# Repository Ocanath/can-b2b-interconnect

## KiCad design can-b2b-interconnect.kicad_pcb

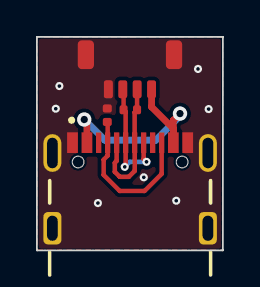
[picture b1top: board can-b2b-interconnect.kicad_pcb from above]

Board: 2 copper layers, 10.3 x 11.9 mm, 4 parts (0 on the bottom side), 5 nets.

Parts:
J2: USB4110GFA; GCT_USB4105-GF-A
R1: 120 0402; R_0402_1005Metric
R3: 5.1k; R_0402_1005Metric
U1: DF52-4S-0.8H(21)

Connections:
/CANH: J2.A6 (DP1), J2.B6 (DP2), R1.2, U1.3
/CANL: J2.A7 (DN1), J2.B7 (DN2), R1.1, U1.2
/VBAT: J2.A4/B9 (VBUS), J2.B4/A9 (VBUS__1), U1.1
GND: J2.A1/B12 (GND), J2.B1/A12 (GND__1), J2.S1 (GND__2), J2.S2 (GND__3), J2.S3 (GND__4), J2.S4 (GND__5), R3.1, U1.4, U1.5 (MNT), U1.6 (MNT)
unnamed: J2.A5 (CC1), J2.B5 (CC2), R3.2

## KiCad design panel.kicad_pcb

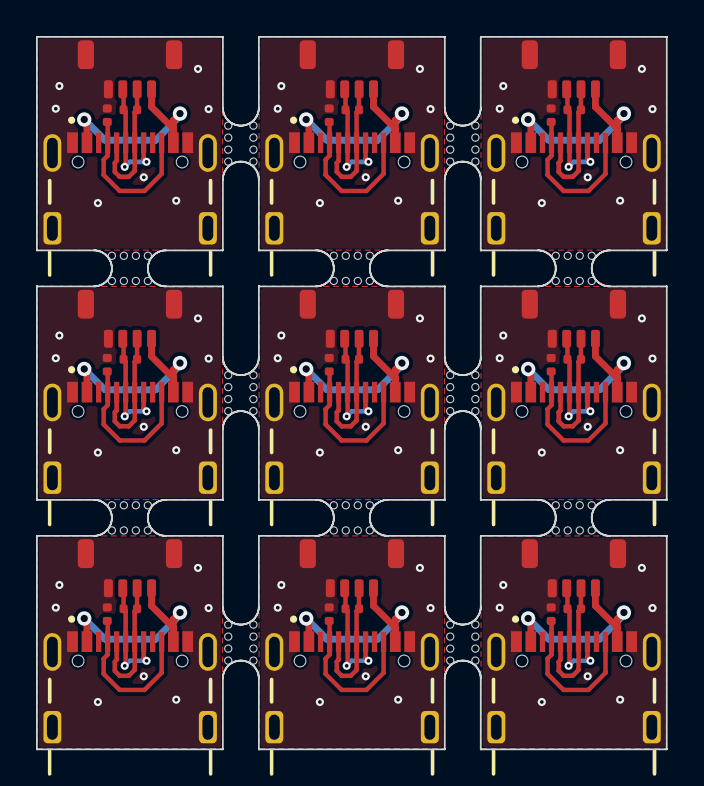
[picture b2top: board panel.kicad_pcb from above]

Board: 2 copper layers, 35.0 x 39.6 mm, 132 parts (0 on the bottom side), 45 nets.

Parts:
J2, J2#2, J2#3, J2#4, J2#5, J2#6, J2#7, J2#8, J2#9: USB4110GFA; GCT_USB4105-GF-A
KiKit_MB_1_1, KiKit_MB_1_2, KiKit_MB_1_3, KiKit_MB_1_4, KiKit_MB_2_1, KiKit_MB_2_2, KiKit_MB_2_3, KiKit_MB_2_4, KiKit_MB_3_1, KiKit_MB_3_2, KiKit_MB_3_3, KiKit_MB_3_4, KiKit_MB_4_1, KiKit_MB_4_2, KiKit_MB_4_3, KiKit_MB_4_4, KiKit_MB_5_1, KiKit_MB_5_2, KiKit_MB_5_3, KiKit_MB_5_4, KiKit_MB_6_1, KiKit_MB_6_2, KiKit_MB_6_3, KiKit_MB_6_4, KiKit_MB_7_1, KiKit_MB_7_2, KiKit_MB_7_3, KiKit_MB_7_4, KiKit_MB_8_1, KiKit_MB_8_2, KiKit_MB_8_3, KiKit_MB_8_4, KiKit_MB_9_1, KiKit_MB_9_2, KiKit_MB_9_3, KiKit_MB_9_4, KiKit_MB_10_1, KiKit_MB_10_2, KiKit_MB_10_3, KiKit_MB_10_4, KiKit_MB_11_1, KiKit_MB_11_2, KiKit_MB_11_3, KiKit_MB_11_4, KiKit_MB_12_1, KiKit_MB_12_2, KiKit_MB_12_3, KiKit_MB_12_4, KiKit_MB_13_1, KiKit_MB_13_2, KiKit_MB_13_3, KiKit_MB_13_4, KiKit_MB_14_1, KiKit_MB_14_2, KiKit_MB_14_3, KiKit_MB_14_4, KiKit_MB_15_1, KiKit_MB_15_2, KiKit_MB_15_3, KiKit_MB_15_4, KiKit_MB_16_1, KiKit_MB_16_2, KiKit_MB_16_3, KiKit_MB_16_4, KiKit_MB_17_1, KiKit_MB_17_2, KiKit_MB_17_3, KiKit_MB_17_4, KiKit_MB_18_1, KiKit_MB_18_2, KiKit_MB_18_3, KiKit_MB_18_4, KiKit_MB_19_1, KiKit_MB_19_2, KiKit_MB_19_3, KiKit_MB_19_4, KiKit_MB_20_1, KiKit_MB_20_2, KiKit_MB_20_3, KiKit_MB_20_4, KiKit_MB_21_1, KiKit_MB_21_2, KiKit_MB_21_3, KiKit_MB_21_4, KiKit_MB_22_1, KiKit_MB_22_2, KiKit_MB_22_3, KiKit_MB_22_4, KiKit_MB_23_1, KiKit_MB_23_2, KiKit_MB_23_3, KiKit_MB_23_4, KiKit_MB_24_1, KiKit_MB_24_2, KiKit_MB_24_3, KiKit_MB_24_4: NPTH
R1, R1#2, R1#3, R1#4, R1#5, R1#6, R1#7, R1#8, R1#9: 120 0402; R_0402_1005Metric
R3, R3#2, R3#3, R3#4, R3#5, R3#6, R3#7, R3#8, R3#9: 5.1k; R_0402_1005Metric
U1, U1#2, U1#3, U1#4, U1#5, U1#6, U1#7, U1#8, U1#9: DF52-4S-0.8H(21)

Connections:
Board_0-/CANH: J2#2.A6 (DP1), J2#2.B6 (DP2), R1#8.2, U1#3.3
Board_0-/CANL: J2#2.A7 (DN1), J2#2.B7 (DN2), R1#8.1, U1#3.2
Board_0-/VBAT: J2#2.A4/B9 (VBUS), J2#2.B4/A9 (VBUS__1), U1#3.1
Board_0-GND: J2#2.A1/B12 (GND), J2#2.B1/A12 (GND__1), J2#2.S1 (GND__2), J2#2.S2 (GND__3), J2#2.S3 (GND__4), J2#2.S4 (GND__5), R3#8.1, U1#3.4, U1#3.5 (MNT), U1#3.6 (MNT)
Board_0-Net-(J2-CC1): J2#2.A5 (CC1), J2#2.B5 (CC2), R3#8.2
Board_1-/CANH: J2#7.A6 (DP1), J2#7.B6 (DP2), R1#2.2, U1#6.3
Board_1-/CANL: J2#7.A7 (DN1), J2#7.B7 (DN2), R1#2.1, U1#6.2
Board_1-/VBAT: J2#7.A4/B9 (VBUS), J2#7.B4/A9 (VBUS__1), U1#6.1
Board_1-GND: J2#7.A1/B12 (GND), J2#7.B1/A12 (GND__1), J2#7.S1 (GND__2), J2#7.S2 (GND__3), J2#7.S3 (GND__4), J2#7.S4 (GND__5), R3#7.1, U1#6.4, U1#6.5 (MNT), U1#6.6 (MNT)
Board_1-Net-(J2-CC1): J2#7.A5 (CC1), J2#7.B5 (CC2), R3#7.2
Board_2-/CANH: J2#8.A6 (DP1), J2#8.B6 (DP2), R1#5.2, U1#8.3
Board_2-/CANL: J2#8.A7 (DN1), J2#8.B7 (DN2), R1#5.1, U1#8.2
Board_2-/VBAT: J2#8.A4/B9 (VBUS), J2#8.B4/A9 (VBUS__1), U1#8.1
Board_2-GND: J2#8.A1/B12 (GND), J2#8.B1/A12 (GND__1), J2#8.S1 (GND__2), J2#8.S2 (GND__3), J2#8.S3 (GND__4), J2#8.S4 (GND__5), R3.1, U1#8.4, U1#8.5 (MNT), U1#8.6 (MNT)
Board_2-Net-(J2-CC1): J2#8.A5 (CC1), J2#8.B5 (CC2), R3.2
Board_3-/CANH: J2.A6 (DP1), J2.B6 (DP2), R1#9.2, U1#4.3
Board_3-/CANL: J2.A7 (DN1), J2.B7 (DN2), R1#9.1, U1#4.2
Board_3-/VBAT: J2.A4/B9 (VBUS), J2.B4/A9 (VBUS__1), U1#4.1
Board_3-GND: J2.A1/B12 (GND), J2.B1/A12 (GND__1), J2.S1 (GND__2), J2.S2 (GND__3), J2.S3 (GND__4), J2.S4 (GND__5), R3#6.1, U1#4.4, U1#4.5 (MNT), U1#4.6 (MNT)
Board_3-Net-(J2-CC1): J2.A5 (CC1), J2.B5 (CC2), R3#6.2
Board_4-/CANH: J2#5.A6 (DP1), J2#5.B6 (DP2), R1.2, U1#5.3
Board_4-/CANL: J2#5.A7 (DN1), J2#5.B7 (DN2), R1.1, U1#5.2
Board_4-/VBAT: J2#5.A4/B9 (VBUS), J2#5.B4/A9 (VBUS__1), U1#5.1
Board_4-GND: J2#5.A1/B12 (GND), J2#5.B1/A12 (GND__1), J2#5.S1 (GND__2), J2#5.S2 (GND__3), J2#5.S3 (GND__4), J2#5.S4 (GND__5), R3#4.1, U1#5.4, U1#5.5 (MNT), U1#5.6 (MNT)
Board_4-Net-(J2-CC1): J2#5.A5 (CC1), J2#5.B5 (CC2), R3#4.2
Board_5-/CANH: J2#9.A6 (DP1), J2#9.B6 (DP2), R1#7.2, U1.3
Board_5-/CANL: J2#9.A7 (DN1), J2#9.B7 (DN2), R1#7.1, U1.2
Board_5-/VBAT: J2#9.A4/B9 (VBUS), J2#9.B4/A9 (VBUS__1), U1.1
Board_5-GND: J2#9.A1/B12 (GND), J2#9.B1/A12 (GND__1), J2#9.S1 (GND__2), J2#9.S2 (GND__3), J2#9.S3 (GND__4), J2#9.S4 (GND__5), R3#5.1, U1.4, U1.5 (MNT), U1.6 (MNT)
Board_5-Net-(J2-CC1): J2#9.A5 (CC1), J2#9.B5 (CC2), R3#5.2
Board_6-/CANH: J2#6.A6 (DP1), J2#6.B6 (DP2), R1#6.2, U1#9.3
Board_6-/CANL: J2#6.A7 (DN1), J2#6.B7 (DN2), R1#6.1, U1#9.2
Board_6-/VBAT: J2#6.A4/B9 (VBUS), J2#6.B4/A9 (VBUS__1), U1#9.1
Board_6-GND: J2#6.A1/B12 (GND), J2#6.B1/A12 (GND__1), J2#6.S1 (GND__2), J2#6.S2 (GND__3), J2#6.S3 (GND__4), J2#6.S4 (GND__5), R3#9.1, U1#9.4, U1#9.5 (MNT), U1#9.6 (MNT)
Board_6-Net-(J2-CC1): J2#6.A5 (CC1), J2#6.B5 (CC2), R3#9.2
Board_7-/CANH: J2#3.A6 (DP1), J2#3.B6 (DP2), R1#3.2, U1#2.3
Board_7-/CANL: J2#3.A7 (DN1), J2#3.B7 (DN2), R1#3.1, U1#2.2
Board_7-/VBAT: J2#3.A4/B9 (VBUS), J2#3.B4/A9 (VBUS__1), U1#2.1
Board_7-GND: J2#3.A1/B12 (GND), J2#3.B1/A12 (GND__1), J2#3.S1 (GND__2), J2#3.S2 (GND__3), J2#3.S3 (GND__4), J2#3.S4 (GND__5), R3#3.1, U1#2.4, U1#2.5 (MNT), U1#2.6 (MNT)
Board_7-Net-(J2-CC1): J2#3.A5 (CC1), J2#3.B5 (CC2), R3#3.2
Board_8-/CANH: J2#4.A6 (DP1), J2#4.B6 (DP2), R1#4.2, U1#7.3
Board_8-/CANL: J2#4.A7 (DN1), J2#4.B7 (DN2), R1#4.1, U1#7.2
Board_8-/VBAT: J2#4.A4/B9 (VBUS), J2#4.B4/A9 (VBUS__1), U1#7.1
Board_8-GND: J2#4.A1/B12 (GND), J2#4.B1/A12 (GND__1), J2#4.S1 (GND__2), J2#4.S2 (GND__3), J2#4.S3 (GND__4), J2#4.S4 (GND__5), R3#2.1, U1#7.4, U1#7.5 (MNT), U1#7.6 (MNT)
Board_8-Net-(J2-CC1): J2#4.A5 (CC1), J2#4.B5 (CC2), R3#2.2

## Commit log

2024-08-05 init commit
2024-08-05 steps
2024-08-05 board designed. needs to be panelized, gotta revisit that tool...
2024-08-05 not routed yet, sch
2024-08-05 df52 to two usbcs, with optional termination resistor
2024-08-05 board designed
2024-08-05 added some vias
2024-08-05 fix clearance issue
2024-08-07 panel
2024-08-07 updated gnd for panel. updated panel. updated panel script for better more better
2024-08-07 panel order
